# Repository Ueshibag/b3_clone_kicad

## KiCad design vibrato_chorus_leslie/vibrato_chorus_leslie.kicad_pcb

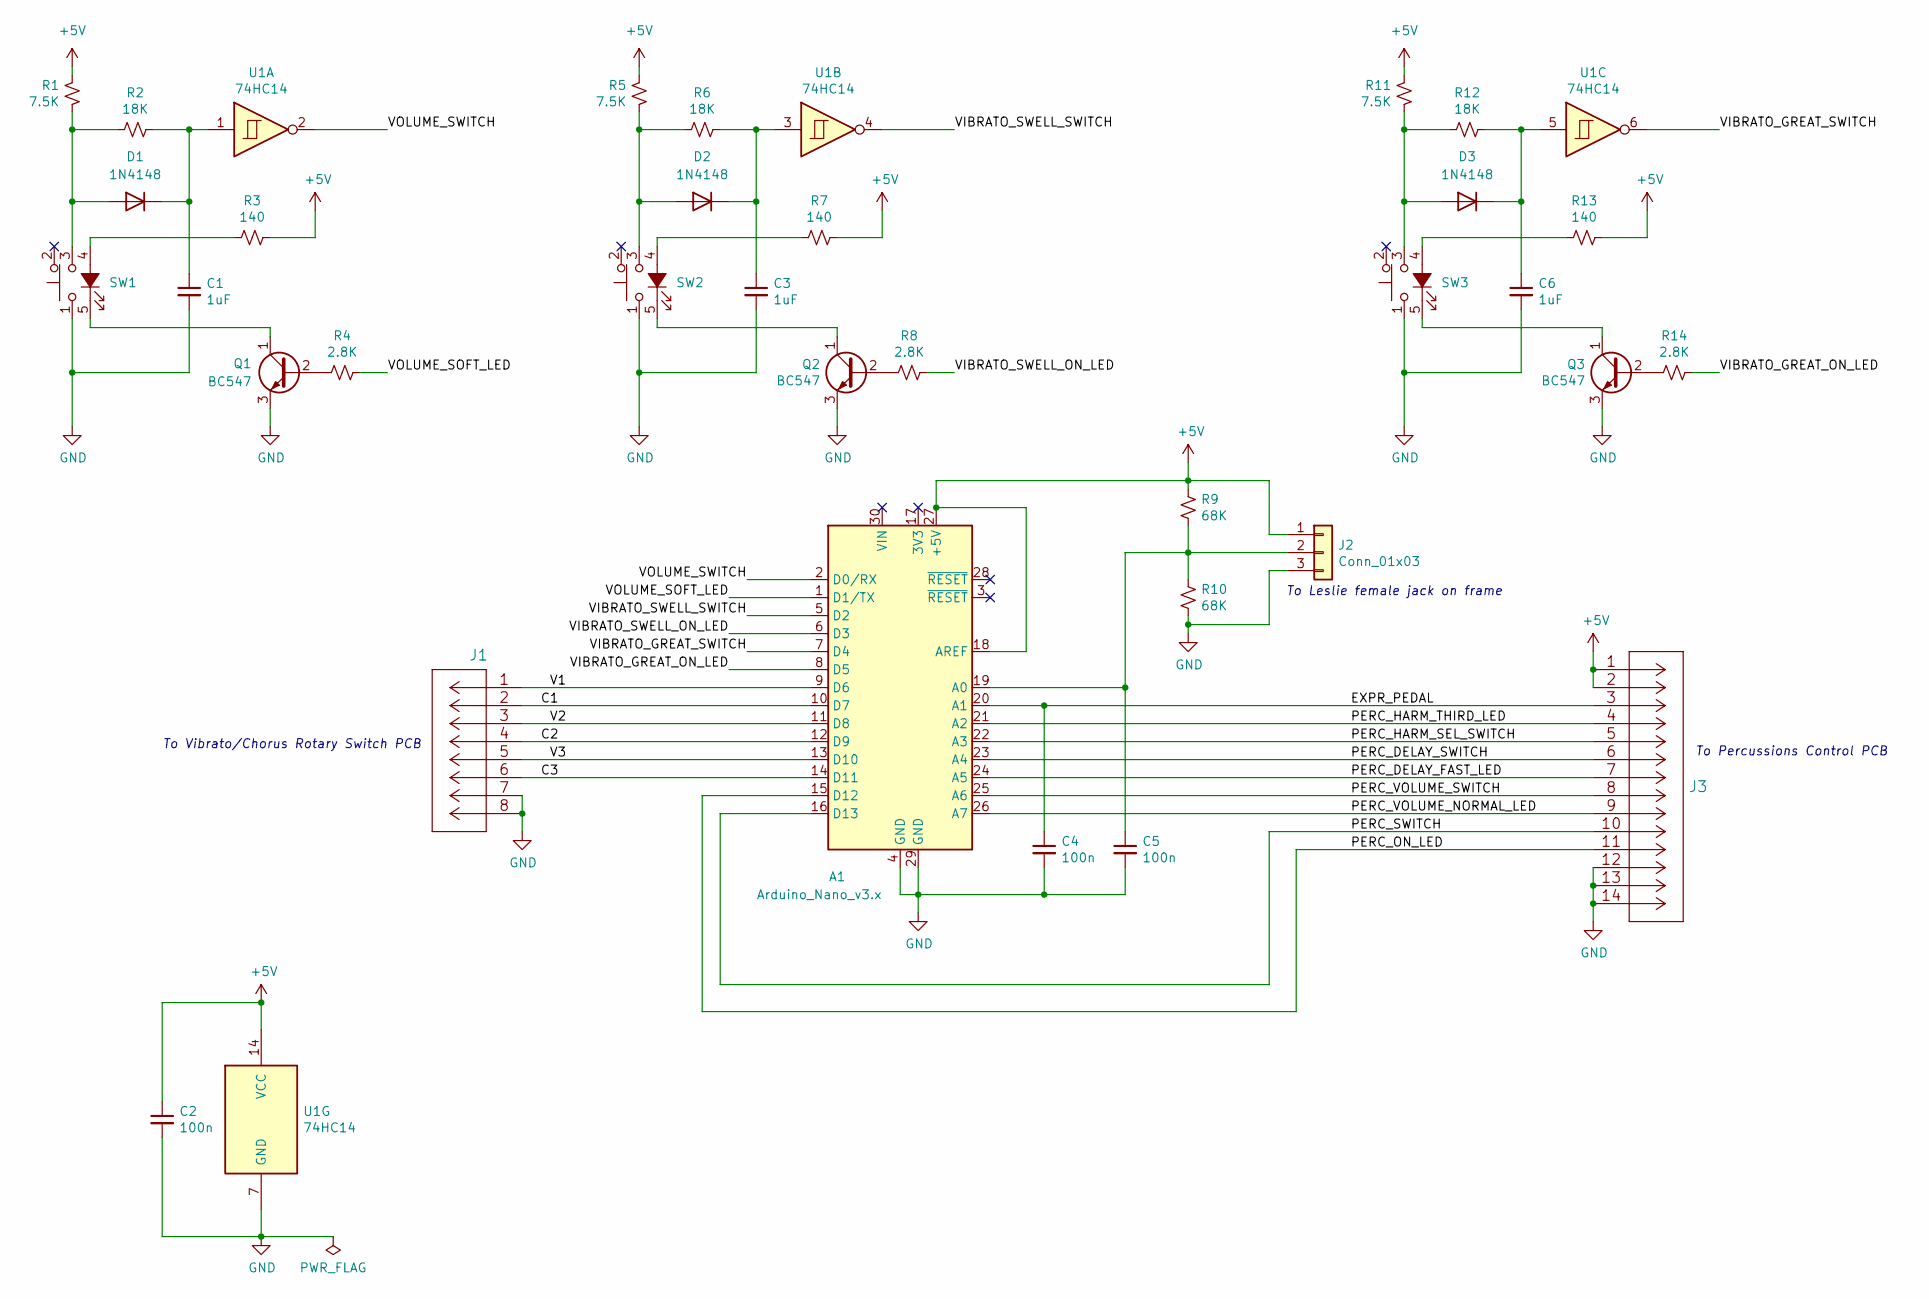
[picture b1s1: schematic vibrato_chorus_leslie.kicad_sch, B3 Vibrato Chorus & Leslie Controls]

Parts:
A1: Arduino_Nano_v3.x; Arduino_Nano
C1, C3, C6: 1uF; C_1206_3216Metric_Pad1.33x1.80mm_HandSolder
C2, C4, C5: 100n; C_1206_3216Metric_Pad1.33x1.80mm_HandSolder
D1, D2, D3: 1N4148; D_DO-35_SOD27_P7.62mm_Horizontal
J1: 7-215079-8; MicroMatch_2x04_P1.27mm_Vertical
J2: Conn_01x03; PinHeader_1x03_P2.54mm_Vertical
J3: 8-215079-4; MicroMatch_2x07_P1.27mm_Vertical
Q1, Q2, Q3: BC547; TO-92_Inline
R1, R5, R11: 7.5K; R_1206_3216Metric_Pad1.30x1.75mm_HandSolder
R2, R6, R12: 18K; R_1206_3216Metric_Pad1.30x1.75mm_HandSolder
R3, R7, R13: 140; R_1206_3216Metric_Pad1.30x1.75mm_HandSolder
R4, R8, R14: 2.8K; R_1206_3216Metric_Pad1.30x1.75mm_HandSolder
R9, R10: 68K; R_1206_3216Metric_Pad1.30x1.75mm_HandSolder
SW1, SW2, SW3: E-SWITCH-SW_Push_LED; 5511MBLKRED
U1: 74HC14; SOIC-14_3.9x8.7mm_P1.27mm

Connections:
+5V: A1.18 (AREF), A1.27 (+5V), C2.1, J2.1, J3.1, J3.2, R1.1, R3.1, R5.1, R7.1, R9.1, R11.1, R13.1, U1.14 (VCC)
/C1: A1.10 (D7), J1.2
/C2: A1.12 (D9), J1.4
/C3: A1.14 (D11), J1.6
/EXPR_PEDAL: A1.20 (A1), C4.1, J3.3
/PERC_DELAY_FAST_LED: A1.24 (A5), J3.7
/PERC_DELAY_SWITCH: A1.23 (A4), J3.6
/PERC_HARM_SEL_SWITCH: A1.22 (A3), J3.5
/PERC_HARM_THIRD_LED: A1.21 (A2), J3.4
/PERC_ON_LED: A1.15 (D12), J3.11
/PERC_SWITCH: A1.16 (D13), J3.10
/PERC_VOLUME_NORMAL_LED: A1.26 (A7), J3.9
/PERC_VOLUME_SWITCH: A1.25 (A6), J3.8
/V1: A1.9 (D6), J1.1
/V2: A1.11 (D8), J1.3
/V3: A1.13 (D10), J1.5
/VIBRATO_GREAT_ON_LED: A1.8 (D5), R14.1
/VIBRATO_GREAT_SWITCH: A1.7 (D4), U1.6
/VIBRATO_SWELL_ON_LED: A1.6 (D3), R8.1
/VIBRATO_SWELL_SWITCH: A1.5 (D2), U1.4
/VOLUME_SOFT_LED: A1.1 (D1/TX), R4.1
/VOLUME_SWITCH: A1.2 (D0/RX), U1.2
GND: A1.4 (GND), A1.29 (GND), C1.2, C2.2, C3.2, C4.2, C5.2, C6.2, J1.7, J1.8, J2.3, J3.12, J3.13, J3.14, Q1.3 (E), Q2.3 (E), Q3.3 (E), R10.2, SW1.1, SW2.1, SW3.1, U1.7 (GND), U1.9, U1.11, U1.13
unnamed: A1.19 (A0), C5.1, J2.2, R9.2, R10.1
unnamed: C1.1, D1.1 (K), R2.1, U1.1
unnamed: C3.1, D2.1 (K), R6.1, U1.3
unnamed: C6.1, D3.1 (K), R12.1, U1.5
unnamed: D1.2 (A), R1.2, R2.2, SW1.3
unnamed: D2.2 (A), R5.2, R6.2, SW2.3
unnamed: D3.2 (A), R11.2, R12.2, SW3.3
unnamed: Q1.1 (C), SW1.5 (K)
unnamed: Q1.2 (B), R4.2
unnamed: Q2.1 (C), SW2.5 (K)
unnamed: Q2.2 (B), R8.2
unnamed: Q3.1 (C), SW3.5 (K)
unnamed: Q3.2 (B), R14.2
unnamed: R3.2, SW1.4 (A)
unnamed: R7.2, SW2.4 (A)
unnamed: R13.2, SW3.4 (A)

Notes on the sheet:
To Leslie female jack on frame
To Percussions Control PCB
To Vibrato/Chorus Rotary Switch PCB

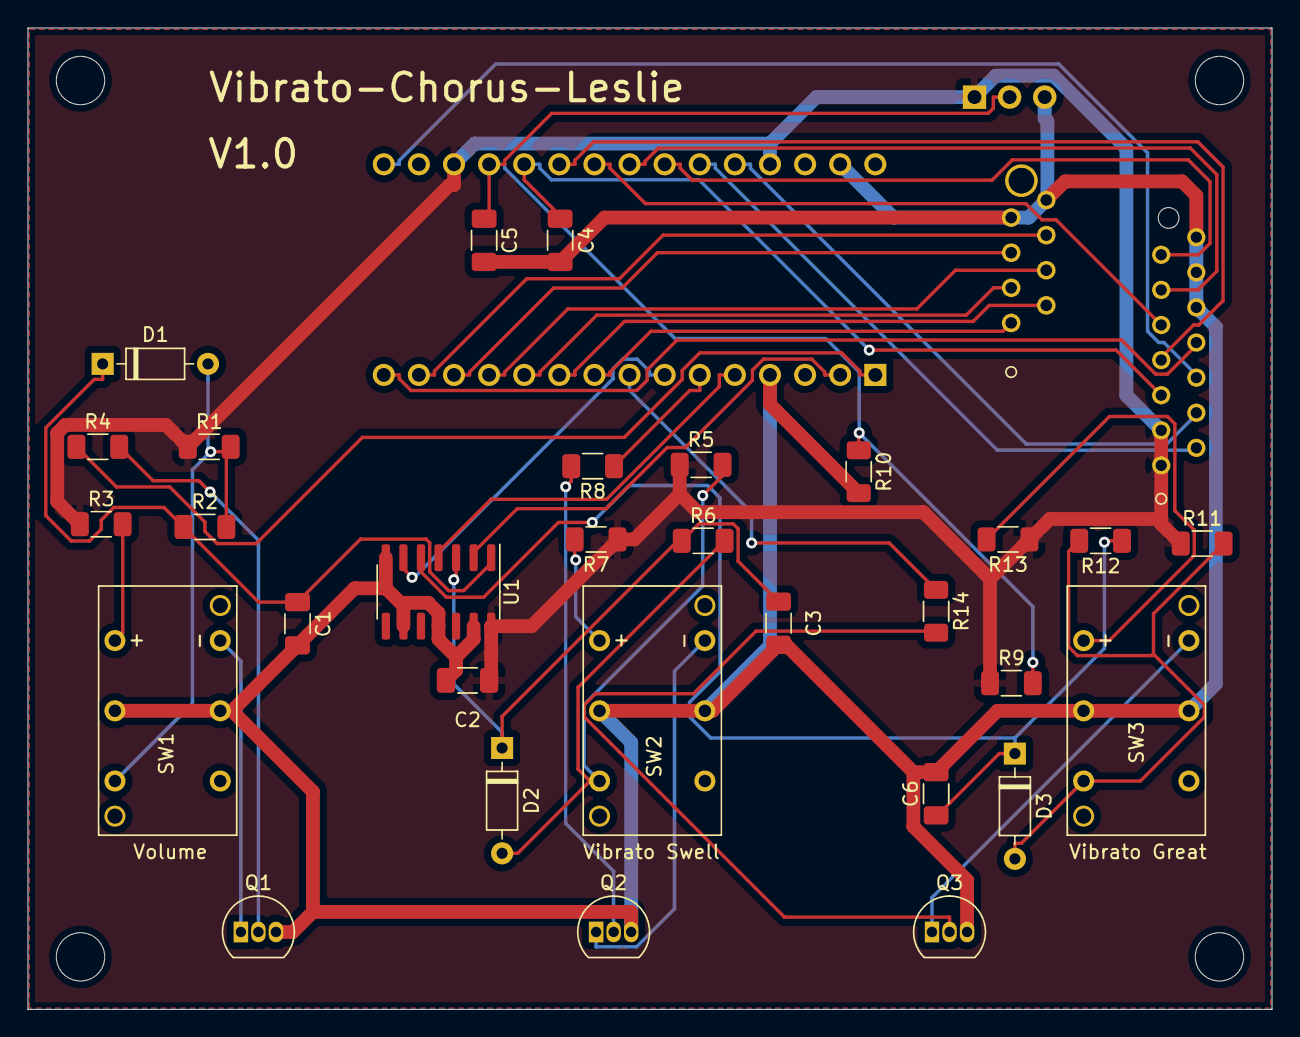
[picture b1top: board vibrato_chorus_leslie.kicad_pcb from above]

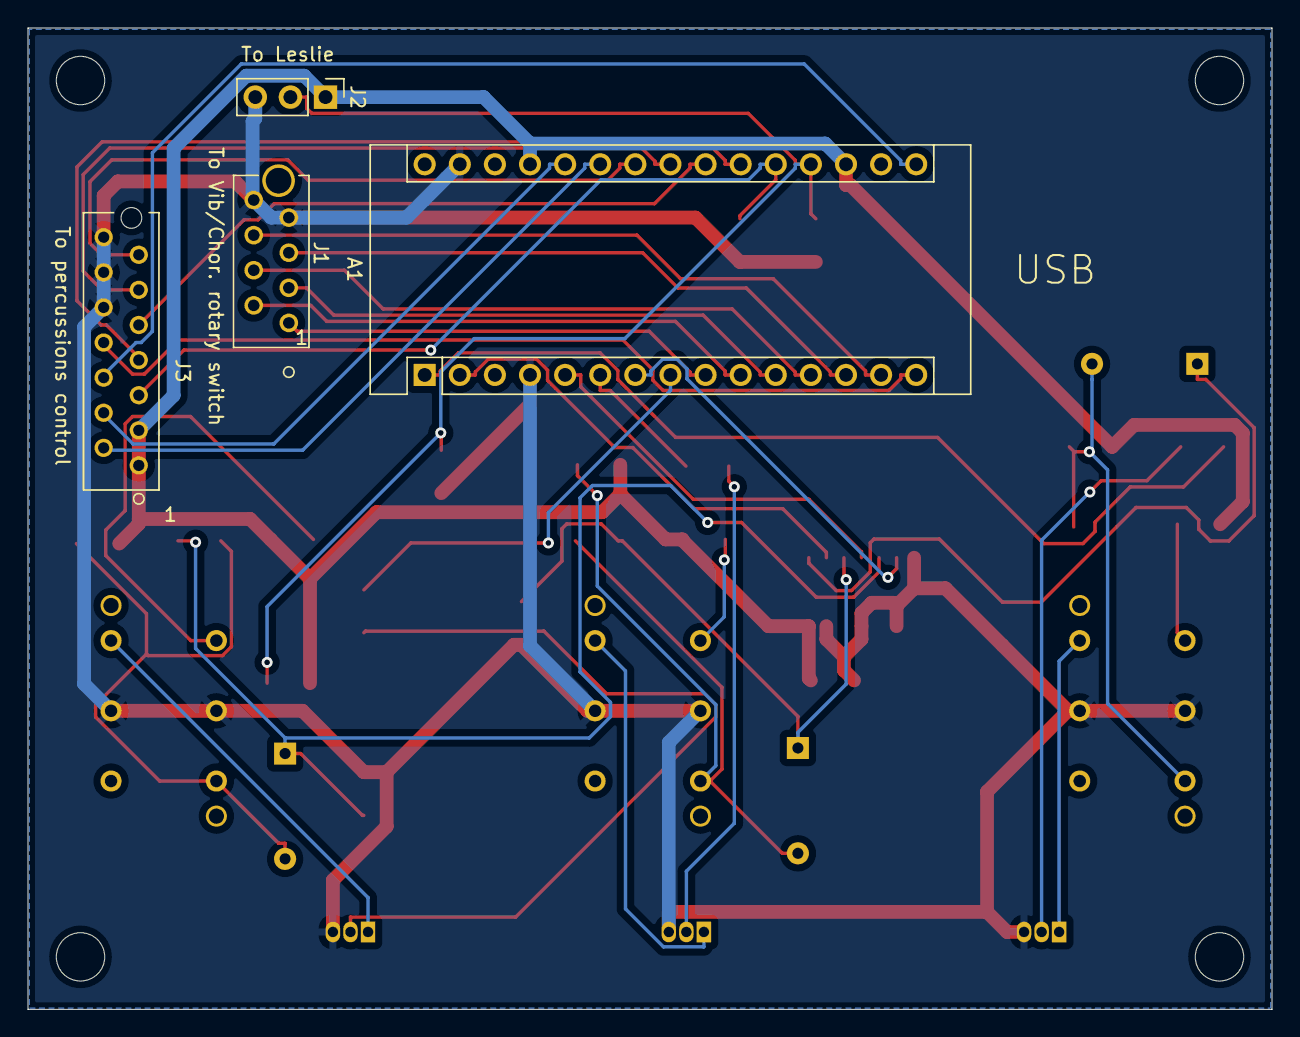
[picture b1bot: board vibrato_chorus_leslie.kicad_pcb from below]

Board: 2 copper layers, 90.0 x 71.0 mm, 38 parts (4 on the bottom side), 39 nets.

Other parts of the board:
REF0, REF1, REF2, REF3: MountingHole_3.5mm

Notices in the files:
parts and their libraries:
Copyright 2021 Accelerated Designs. All rights reserved.
